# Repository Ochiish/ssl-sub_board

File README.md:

# SubBoard for SSL

## Overview

This is a sub-board installed in the SSL robot.
The boost circuit, neopixel, phototransistor, etc. are controlled by stm32, and CAN communication is performed with the main board.

## Requirement

- KiCad 7.0.5

## Usage

Good luck...

## Features

This is a sub-board installed in an SSL robot. The board is equipped with various components such as a boost circuit, NeoPixels, phototransistors, etc., all controlled by an STM32 microcontroller. 

- This microcontroller offers advanced programming and processing capabilities, efficiently managing the robot's diverse functions.

- The boost circuit optimizes power supply, ensuring each component on the board operates at the correct voltage. It elevates the low voltage from the battery, distributing power as needed.

- NeoPixels are individually controllable LEDs used for visual feedback and status indication on the robot. These LEDs can be customized in color and brightness through programming, intuitively conveying the robot's status to the operator.

- Phototransistors detect light intensity and convert this information into digital signals. This is a crucial sensor for environmental awareness and obstacle detection in the robot.

- Furthermore, this robot is equipped with a thermistor for measuring the temperature of the solenoid coil. The thermistor plays a vital role in monitoring the heat generated by the solenoid, preventing overheating and enhancing the robot's safety and equipment lifespan.

- Additionally, the sub-board incorporates protective circuits around the power supply, safeguarding it against overvoltage and short circuits. 

- These circuits are essential for maintaining power stability while minimizing electrical risks.

- The sub-board communicates with the main board using the CAN communication protocol. CAN communication is known for its high reliability and error detection capabilities, ensuring secure data exchange between different parts of the robot. This allows for smooth overall operation and the ability to perform more complex tasks.

In this way, the sub-board supports crucial functions of the SSL robot, drawing out the robot's maximum performance through advanced technology and meticulous design.

## Reference

https://www.analog.com/media/jp/technical-documentation/data-sheets/j3751fc.pdf

## Author

[@Allsatako](http://twitter.com/Allsatako)

mail to: rionesslq@gmail.com

## Licence

There is no license as this is open source hardware.

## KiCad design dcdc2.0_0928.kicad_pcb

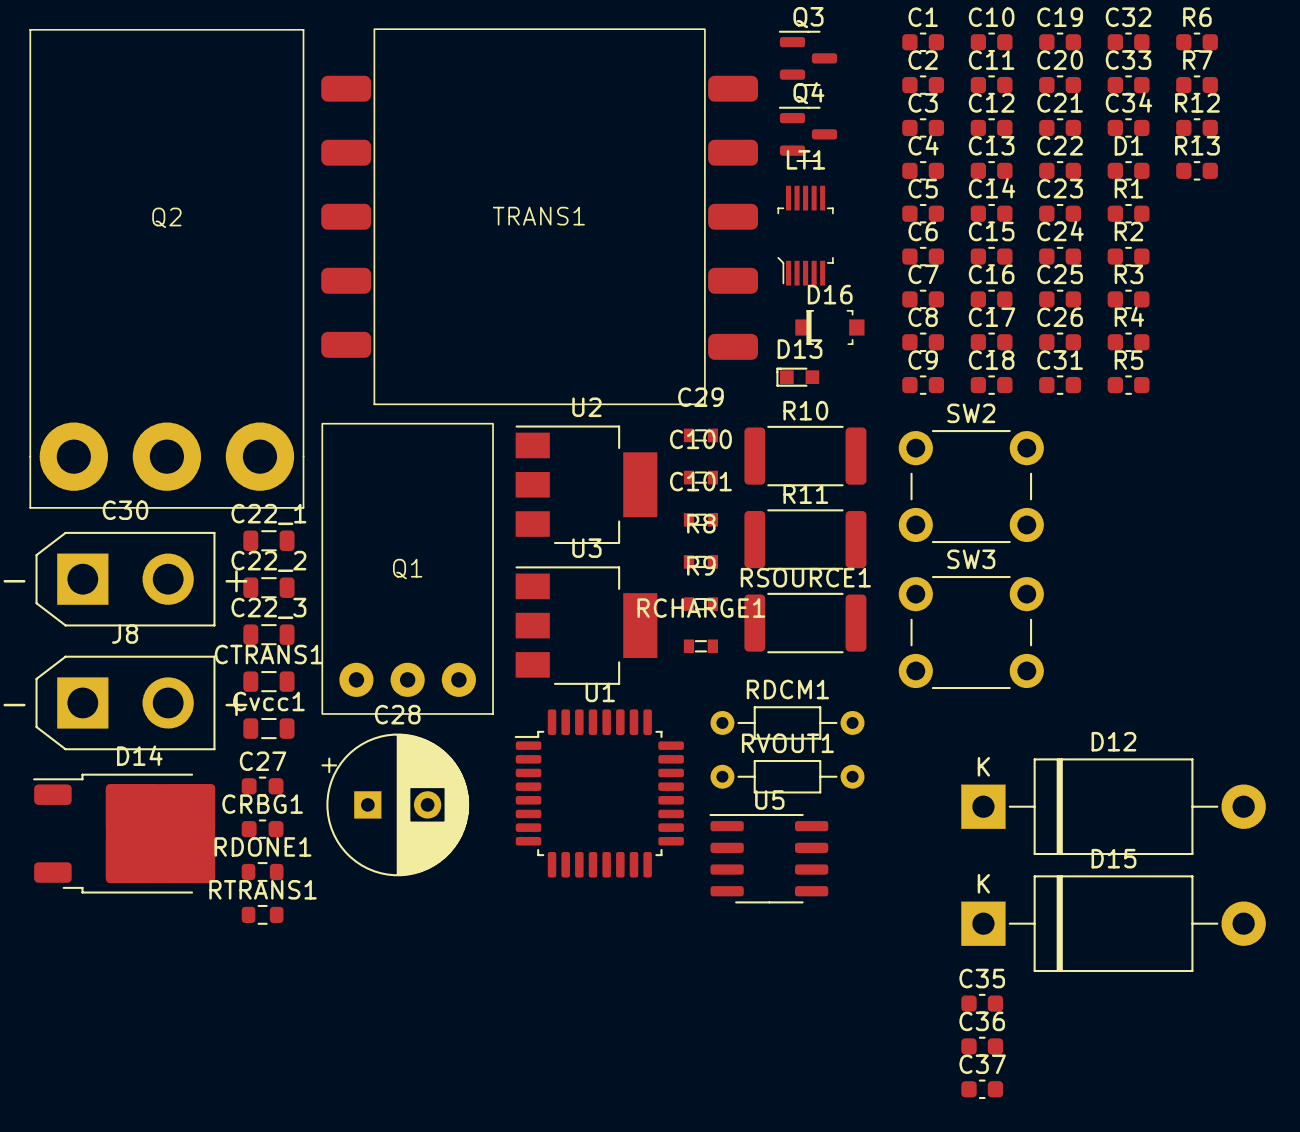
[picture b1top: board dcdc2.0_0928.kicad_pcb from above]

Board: 2 copper layers, 83 parts (0 on the bottom side), 33 nets, no tracks yet.

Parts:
C1, C2, C3, C4, C5, C6, C7, C11, C12, C13, C14, C15, C16, C17, C18, C19, C20, C21, C22, C23, C24, C25, C26, C32, C33, C34, C35, C36, C37: 0.1uF; C_0603_1608Metric
C8, C10: 4.3pF; C_0603_1608Metric
C9: 4.7uF; C_0603_1608Metric
C22_1, C22_2, C22_3: 22uF; L_0805_2012Metric
C27: 1000pf; L_0603_1608Metric
C28: 150uF 35v; CP_Radial_D8.0mm_P3.50mm
C29, C101: 0.1uF; 0603
C30: 2200uF; AMASS_XT30UPB-F_1x02_P5.0mm_Vertical
C31: 22uF; C_0603_1608Metric
C100: 10uF; 0603
CRBG1: 51pF; L_0603_1608Metric
CTRANS1: 10uF 50v; L_0805_2012Metric
Cvcc1: 10uF; L_0805_2012Metric
D1: LED; C_0603_1608Metric
D12, D15: 1.5KExxA; D_DO-201AE_P15.24mm_Horizontal
D13: LED; LED_0603
D14: 1N4007G; TO-252-2
D16: 1N47xxA; SOD-123
J8: Conn_01x02_Pin; AMASS_XT30UPB-F_1x02_P5.0mm_Vertical
LT1: MSOP-10_W3mm
Q1: tk20a60u
Q2: IRFP150NPbF
Q3, Q4: MMBT3906; SOT-23
R1, R2, R3, R6, R7: 10k; C_0603_1608Metric
R4: 470; C_0603_1608Metric
R5: 20k; C_0603_1608Metric
R8: 100Ω; 0603
R9: 1kΩ; 0603
R10, R11: 120Ω; R_2512_6332Metric
R12, R13: 5k; C_0603_1608Metric
RCHARGE1: 1kΩ; 0603
RDCM1: 42kΩ; R_Axial_DIN0204_L3.6mm_D1.6mm_P7.62mm_Horizontal
RDONE1: 100kΩ; R_0603_1608Metric
RSOURCE1: 0.01Ω; R_2512_6332Metric
RTRANS1: 0Ω; R_0603_1608Metric
RVOUT1: 30kΩ; R_Axial_DIN0204_L3.6mm_D1.6mm_P7.62mm_Horizontal
SW2, SW3: SW_MEC_5E; SW_PUSH_6mm
TRANS1: 32052
U1: STM32F303K8Tx; LQFP-32_7x7mm_P0.8mm
U2: V7805-1000; SOT-223-3_TabPin2
U3: AMS1117-5.0; SOT-223-3_TabPin2
U5: MCP2551-I-SN; SOIC-8_3.9x4.9mm_P1.27mm

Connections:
14v: C22_1.2, C22_2.2, C22_3.2, C28.2, Cvcc1.1, RTRANS1.1, TRANS1.4 (4IN), TRANS1.5 (5IN)
+3V3: C1.2, C3.2, C9.2, U1.1 (VDD), U1.5 (VDDA)
+5V: C4.1, C5.1, C6.1, C7.1, C11.1, C12.1, C13.1, C14.1, C15.1, C16.1, C17.1, C18.1, C19.1, C20.1, C21.1, C22.1, C23.1, C24.1, C25.1, C26.1, C100.2, C101.2, D15.1 (A1), R4.2, R12.1, R13.1, RDONE1.1, U5.3 (VDD)
/drain: RDCM1.2, RVOUT1.2, TRANS1.6 (6IN), TRANS1.7 (7IN)
/drain1: D16.2 (A), J8.2, Q2.3 (D)
/gate1: Q2.2 (G), R8.2, R9.2
/source: Q1.3 (S), RSOURCE1.2
/source1: Q2.1 (S), R9.1
CANH: R10.2, R11.1, U5.7 (CANH)
CANL: R10.1, R11.2, U5.6 (CANL)
CANRX: U1.21 (PA11), U5.4 (RXD)
CANTX: U1.22 (PA12), U5.1 (TXD)
CHARGE: C27.1, RCHARGE1.2
DIN: R3.1, U1.27 (PB4)
ENCODER_A: R12.2, U1.19 (PA9)
ENCODER_B: R13.2, U1.20 (PA10)
GND: C1.1, C2.1, C3.1, C4.2, C5.2, C6.2, C7.2, C8.2, C9.1, C10.2, C11.2, C12.2, C13.2, C14.2, C15.2, C16.2, C17.2, C18.2, C19.2, C20.2, C21.2, C22.2, C22_1.1, C22_2.1, C22_3.1, C23.2, C24.2, C25.2, C26.2, C27.2, C28.1, C32.2, C33.2, C34.2, C35.1, C36.2, C37.2, C100.1, C101.1, CRBG1.2, CTRANS1.1, Cvcc1.2, D1.1 (K), D13.1 (K), R2.1, R5.1, R6.2, R7.2, RSOURCE1.1, SW2.1, SW2.2, SW3.1, SW3.2, U1.16 (VSS), U1.32 (VSS), U3.1 (GND), U5.2 (VSS), U5.8 (Rs)
GND2: C29.1, C29.2, C30.1, C30.2, D14.1 (K), D16.1 (K), J8.1, TRANS1.10 (10OUT)
unnamed: C2.2, U1.17 (VDD)
unnamed: D1.2 (A), R1.2
unnamed: C34.1, C36.1, D12.2 (A2), U3.2 (VO)
unnamed: D13.2 (A), RCHARGE1.1
unnamed: D14.2 (A), TRANS1.1 (1OUT)
unnamed: C31.1, C32.1, C37.1, D15.2 (A2), U2.2 (VO), U3.3 (VI)
unnamed: Q4.2 (E), R7.1
unnamed: CTRANS1.2, RTRANS1.2
unnamed: Q3.1 (B), Q3.3 (C), Q4.1 (B), R6.1
unnamed: R2.2, U1.31 (BOOT0)
unnamed: R1.1, U1.30 (PB7)
unnamed: C31.2, U2.1 (GND)
unnamed: C35.2, U2.3 (VI)
SYS-SWDIO: U1.23 (PA13), U1.26 (PB3)
TR_SIG: R5.2, U1.6 (PA0)

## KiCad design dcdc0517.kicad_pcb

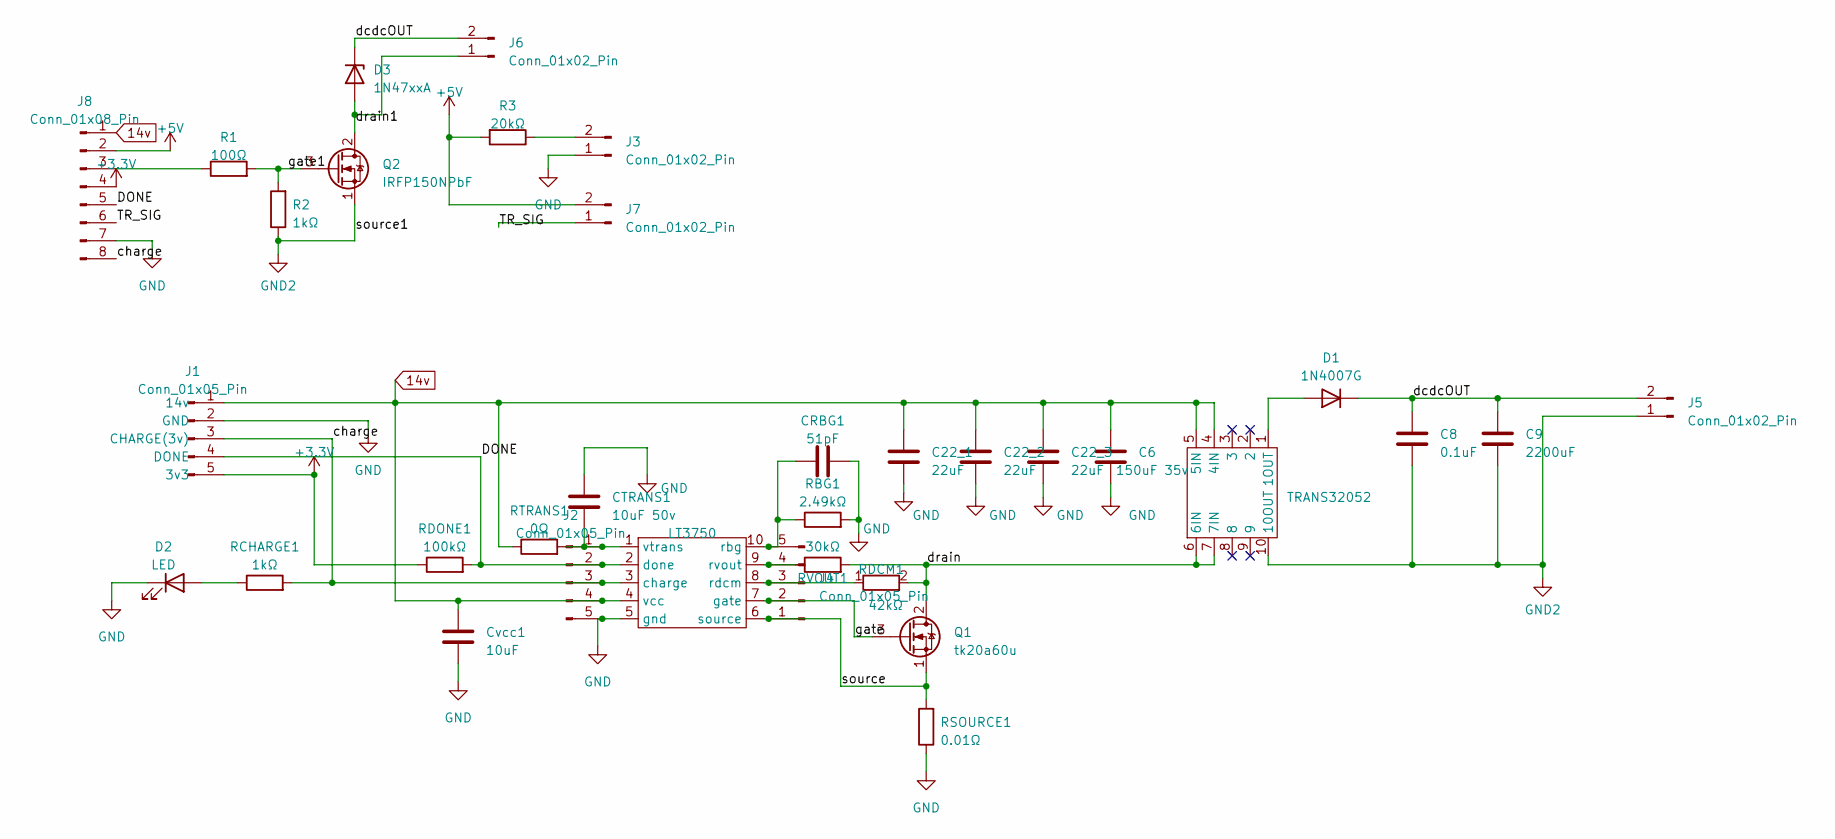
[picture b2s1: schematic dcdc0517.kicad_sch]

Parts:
C6: 150uF 35v; CP_Radial_D8.0mm_P3.50mm
C8: 0.1uF; PinHeader_1x02_P2.54mm_Vertical
C9: 2200uF; AMASS_XT30UPB-F_1x02_P5.0mm_Vertical
C22_1, C22_2, C22_3: 22uF; L_0805_2012Metric
CRBG1: 51pF; L_0603_1608Metric
CTRANS1: 10uF 50v; L_0805_2012Metric
Cvcc1: 10uF; L_0805_2012Metric
D1: 1N4007G; D_DO-35_SOD27_P7.62mm_Horizontal
D2: LED; LED_D3.0mm_FlatTop
D3: 1N47xxA; D_DO-41_SOD81_P10.16mm_Horizontal
J1, J2, J4: Conn_01x05_Pin; PinHeader_1x05_P2.54mm_Vertical
J3, J7: Conn_01x02_Pin; PinHeader_1x02_P2.54mm_Vertical
J5, J6: Conn_01x02_Pin; AMASS_XT30UPB-F_1x02_P5.0mm_Vertical
J8: Conn_01x08_Pin; JST_XH_B8B-XH-AM_1x08_P2.50mm_Vertical
LT3750: MSOP-10_W3mm
Q1: tk20a60u; PinHeader_1x3_P2.54_Drill1.1mm
Q2: IRFP150NPbF; TERM_BLOCK_1x3_P5.08MM
R1: 100Ω; R_0603_1608Metric
R2: 1kΩ; R_0603_1608Metric
R3: 20kΩ; R_0201_0603Metric
RBG1: 2.49kΩ; R_Axial_DIN0204_L3.6mm_D1.6mm_P7.62mm_Horizontal
RCHARGE1: 1kΩ; 0603
RDCM1: 42kΩ; R_Axial_DIN0204_L3.6mm_D1.6mm_P7.62mm_Horizontal
RDONE1: 100kΩ; R_0201_0603Metric
RSOURCE1: 0.01Ω; R_Shunt_Vishay_WSR2_WSR3
RTRANS1: 0Ω; R_Axial_DIN0204_L3.6mm_D1.6mm_P7.62mm_Horizontal
RVOUT1: 30kΩ; R_Axial_DIN0204_L3.6mm_D1.6mm_P7.62mm_Horizontal
TRANS32052: 32052

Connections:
14v: C6.1, C22_1.1, C22_2.1, C22_3.1, Cvcc1.1, J1.1 (14v), J2.4 (vcc), J8.1, LT3750.4 (vcc), RTRANS1.1, TRANS32052.4 (4IN), TRANS32052.5 (5IN)
+3.3V: J1.5 (3v3), J8.4, RDONE1.1
+5V: J7.2, J8.2, R3.2
/DONE: J1.4 (DONE), J2.2 (done), J8.5, LT3750.2 (done), RDONE1.2
/TR_SIG: J7.1, J8.6
/charge: J1.3 (CHARGE(3v)), J2.3 (charge), J8.8, LT3750.3 (charge), RCHARGE1.2
/dcdcOUT: C8.2, C9.2, D1.1 (K), D3.1 (K), J5.2, J6.2
/drain: Q1.2 (D), RDCM1.2, RVOUT1.2, TRANS32052.6 (6IN), TRANS32052.7 (7IN)
/drain1: D3.2 (A), J6.1, Q2.2 (D)
/gate: J4.2 (gate), LT3750.7 (gate), Q1.3 (G)
/gate1: Q2.3 (G), R1.2, R2.2
/source: J4.1 (source), LT3750.6 (source), Q1.1 (S), RSOURCE1.2
GND: C6.2, C22_1.2, C22_2.2, C22_3.2, CRBG1.2, CTRANS1.1, Cvcc1.2, D2.1 (K), J1.2 (GND), J2.5 (gnd), J3.1, J8.7, LT3750.5 (gnd), RBG1.2, RSOURCE1.1
GND2: C8.1, C9.1, J5.1, Q2.1 (S), R2.1, TRANS32052.10 (10OUT)
unnamed: D1.2 (A), TRANS32052.1 (1OUT)
unnamed: D2.2 (A), RCHARGE1.1
unnamed: CTRANS1.2, J2.1 (vtrans), LT3750.1 (vtrans), RTRANS1.2
unnamed: J3.2, R3.1
unnamed: CRBG1.1, J4.5 (rbg), LT3750.10 (rbg), RBG1.1
unnamed: J4.3 (rdcm), LT3750.8 (rdcm), RDCM1.1
unnamed: J4.4 (rvout), LT3750.9 (rvout), RVOUT1.1
unnamed: J8.3, R1.1

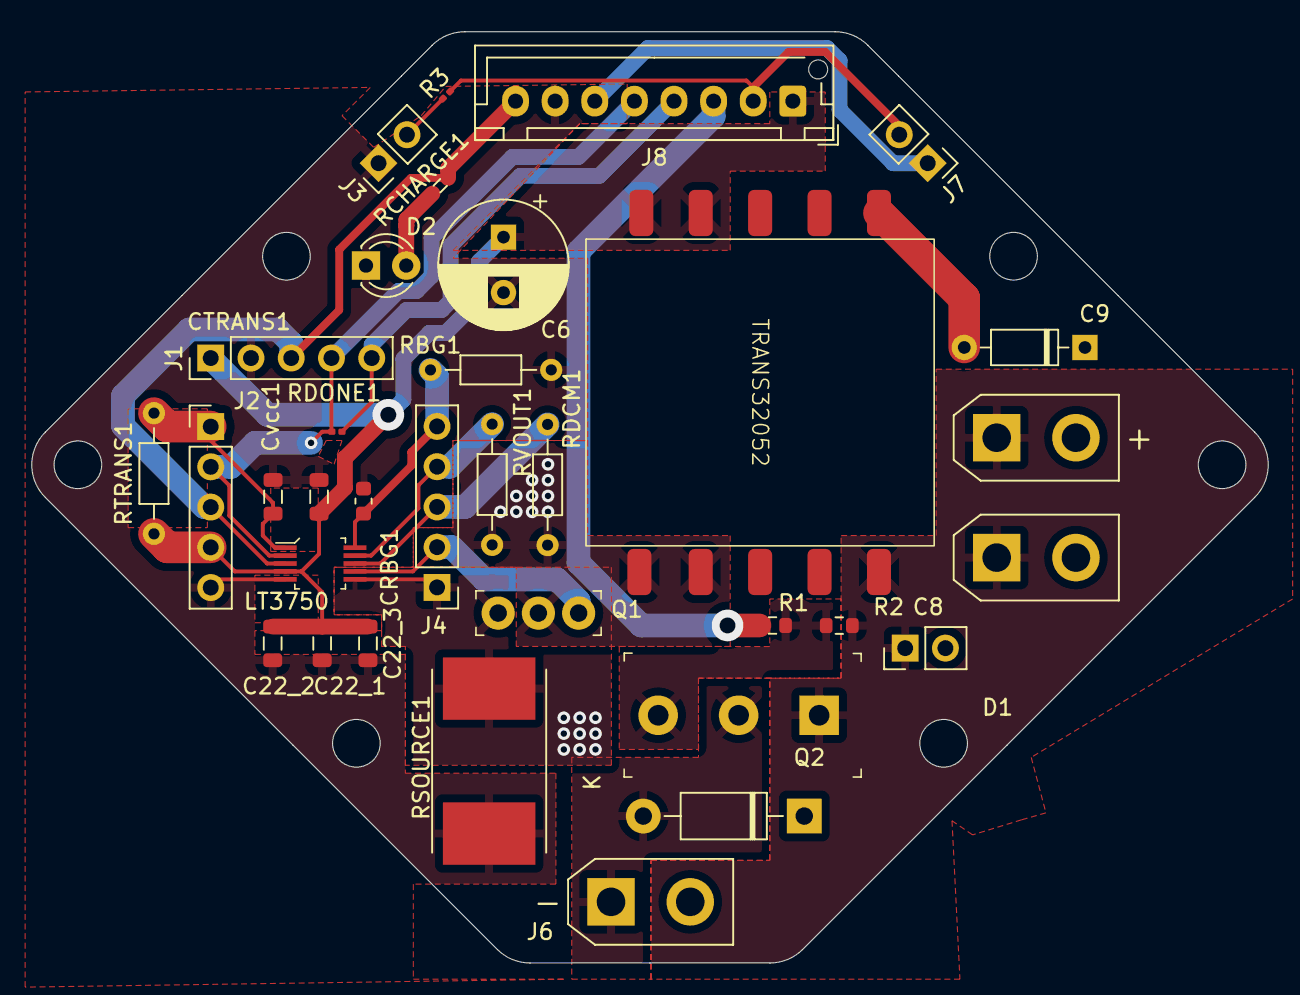
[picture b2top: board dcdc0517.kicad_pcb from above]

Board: 2 copper layers, 78.0 x 58.8 mm, 34 parts (0 on the bottom side), 22 nets.

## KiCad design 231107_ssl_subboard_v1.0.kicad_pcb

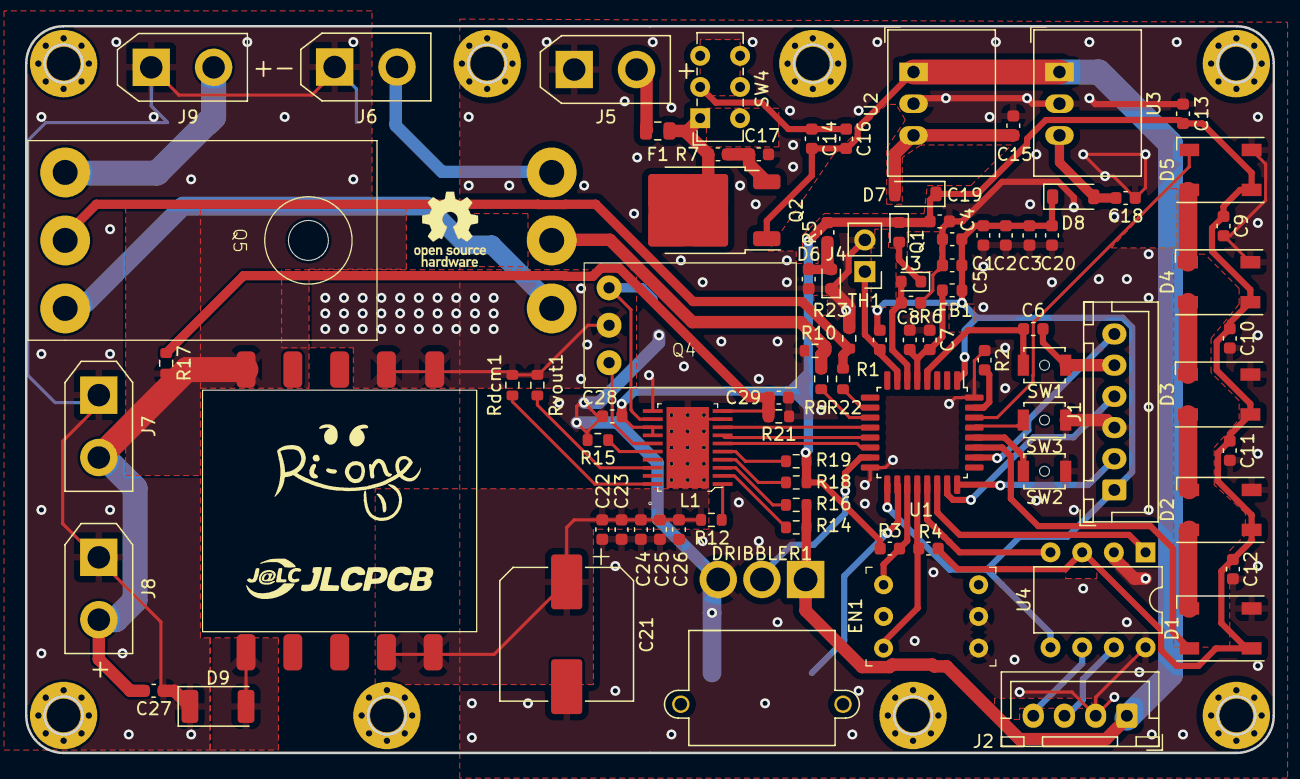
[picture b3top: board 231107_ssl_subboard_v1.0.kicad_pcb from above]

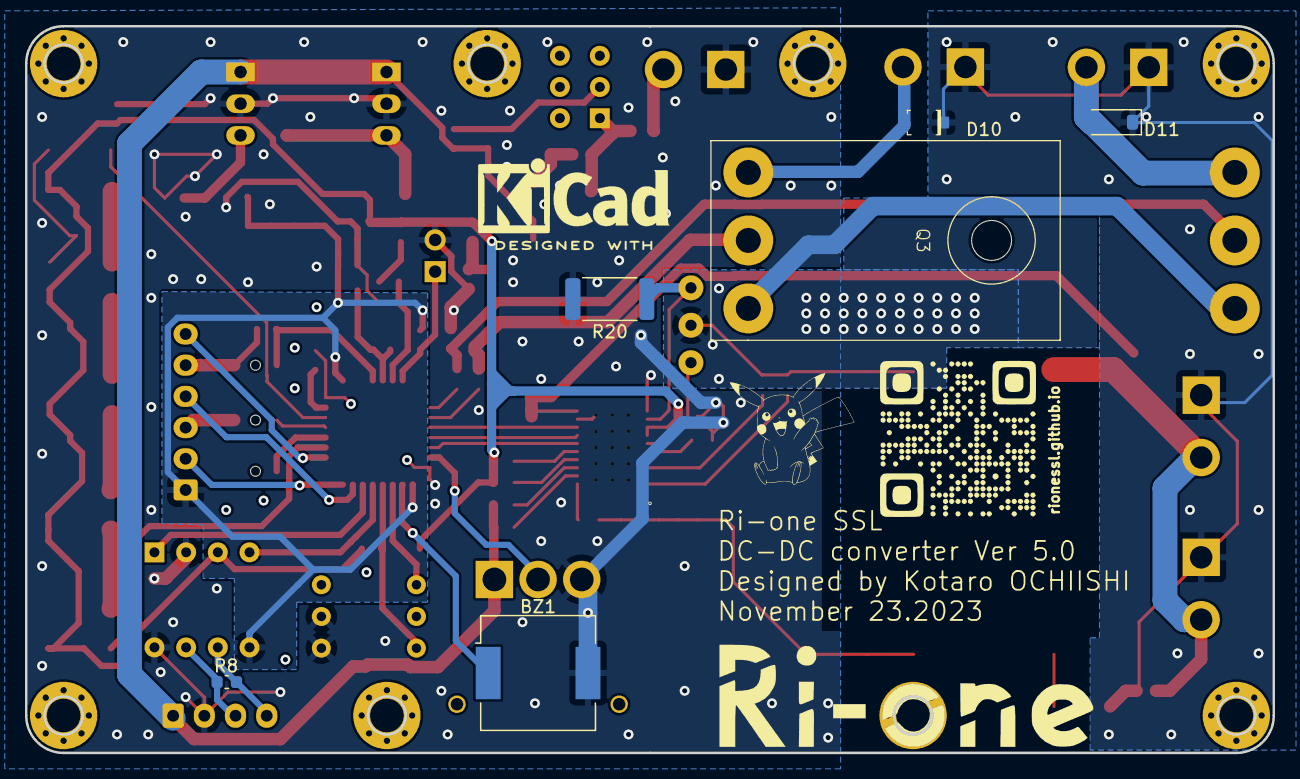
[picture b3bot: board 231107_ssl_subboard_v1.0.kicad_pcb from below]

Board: 2 copper layers, 100.0 x 58.2 mm, 93 parts (6 on the bottom side), 62 nets.

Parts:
BZ1: Buzzer; Buzzer_CUI_CPT-9019S-SMT
C1, C2, C3, C4, C5, C6, C7, C8, C9, C10, C11, C12, C13, C14, C16, C17, C19, C20: 0.1uF; C_0603_1608Metric
C15, C18, C22, C23, C24, C25, C26: 2.2u; C_0603_1608Metric
C21: 680u; CP_Elec_10x10.5
C27: 0.47u; C_0603_1608Metric
C28, C29: 10n; C_0603_1608Metric
D1, D2, D3, D4, D5: ws2812b; LED_Cree-PLCC4_5x5mm_CW
D6: LED; C_0603_1608Metric
D7, D8: SS2040FL; D_SOD-123
D9: 1.5KExxA; D_2010_5025Metric
D10: 1.5KExxA; SOD-123
D11: 1.5KExxA; D_SOD-123
DRIBBLER1: MR30PW-M; AMASS_MR30PW-M_1x03_P3.50mm_Horizontal
EN1: RotaryEncoder_Switch; SOCKET_DIP-6_7.62mm_Conn
F1: Fuse; Fuse_0805_2012Metric
FB1: FerriteBead_Small; L_0603_1608Metric
J1: pc to stm32; JST_XH_B6B-XH-A_1x06_P2.50mm_Vertical
J2: main to sub; JST_XH_B4B-XH-A_1x04_P2.50mm_Vertical
J3: PHOTOCOUPLER; LED_0603_1608Metric
J4: LED; LED_0603_1608Metric
J5: lipo_3cell; AMASS_XT30UPB-M_1x02_P5.0mm_Vertical
J6: s1; AMASS_XT30UPB-F_1x02_P5.0mm_Vertical
J7: c1; AMASS_XT30UPB-F_1x02_P5.0mm_Vertical
J8: c2; AMASS_XT30UPB-F_1x02_P5.0mm_Vertical
J9: s2; AMASS_XT30UPB-F_1x02_P5.0mm_Vertical
L1: TSSOP-20-1EP_W4.4mm
Q1: Q_Photo_NPN; LED_0603_1608Metric
Q2: PMOS; TO-252-2
Q3, Q5: NMOS; IRFP150NPbF
Q4: Q_NMOS_DGS; tk20a60u
R1, R3, R4: 5k; C_0603_1608Metric
R2, R7: 10k; C_0603_1608Metric
R5: 470; C_0603_1608Metric
R6: 20k; C_0603_1608Metric
R8: 120; C_0603_1608Metric
R9, R22: 100; R_0603_1608Metric
R10, R23: 1k; R_0603_1608Metric
R12: 40.2k; R_0603_1608Metric
R14, R18: 69.8k; R_0603_1608Metric
R15: 1.65; R_0603_1608Metric
R16, R19: 475k; R_0603_1608Metric
R17: 124; R_0603_1608Metric
R20: 6m; R_2512_6332Metric
R21: 0.768k; R_0603_1608Metric
Rdcm1: 18.2k; R_0603_1608Metric
Rvout1: 40.2k; R_0603_1608Metric
SW1, SW2, SW3: SW_Push; SW_SPST_B3U-1000P-B
SW4: SW_SPST; SW_E-Switch_EG1271_SPDT
TH1: Thermistor; PinHeader_1x02_P2.54mm_Vertical
U1: STM32F303K8Tx; LQFP-32_7x7mm_P0.8mm
U2: M78AR05-1; Converter_DCDC_RECOM_R-78E-0.5_THT
U3: M78AR033-1; Converter_DCDC_RECOM_R-78E-0.5_THT
U4: MCP2562-E-P; DIP-8_W7.62mm
U5: 32052

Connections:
+3V3: C1.2, C2.2, C3.2, C4.2, C5.2, C20.2, D8.1 (K), FB1.1, J1.1, R1.2, U1.1 (VDD), U1.17 (VDD), U4.5 (Vio)
+5V: C9.1, C10.1, C11.1, C12.1, C13.1, C19.2, C28.1, D1.3 (VDD), D2.3 (VDD), D3.3 (VDD), D4.3 (VDD), D5.3 (VDD), D7.1 (K), L1.13 (VCC), L1.14 (LVGATE), Q1.1 (C), R3.1, R4.1, R5.2, R18.1, R19.1, U4.3 (VDD)
+15V: C14.2, C16.2, DRIBBLER1.1, J2.1, Q2.1 (D), R14.1, R16.1, U2.1 (IN), U3.1 (IN)
+BATT: F1.1, J5.2
CANH: J2.3, R8.2, U4.7 (CANH)
CANL: J2.4, R8.1, U4.6 (CANL)
CANRX: U1.21 (PA11), U4.4 (RXD)
CANTX: U1.22 (PA12), U4.1 (TXD)
CHARGE: L1.8 (CHARGE), U1.12 (PA6)
Cvtrans: C21.1, C22.1, C23.1, C24.1, C25.1, C26.1, R12.1, U5.4 (4IN), U5.5 (5IN)
DCDC_OUT: C27.1, D9.1 (A1), D10.1 (A1), D11.1 (A1), J6.1, J7.1, J8.1, J9.1
DIN: D1.4 (DIN), U1.27 (PB4)
DONE: L1.7 (DONE), U1.13 (PA7)
DOUT: D5.1 (DOUT), U1.30 (PB7)
DR_PWM: DRIBBLER1.2, U1.15 (PB1)
DR_SW: SW3.2, U1.29 (PB6)
Drain: Q4.1 (D), Rdcm1.2, Rvout1.2, U5.6 (6IN), U5.7 (7IN)
ENCODER_A: EN1.1 (A), R3.2, U1.19 (PA9)
ENCODER_B: EN1.3 (B), R4.2, U1.20 (PA10)
FAULT: L1.6 (FAULT), U1.14 (PB0)
GND: BZ1.2 (+), C1.1, C2.1, C3.1, C4.1, C5.1, C7.1, C8.1, C9.2, C10.2, C11.2, C12.2, C13.2, C15.1, C17.1, C18.1, C19.1, C20.1, C21.2, C22.2, C23.2, C24.2, C25.2, C26.2, C28.2, C29.2, D1.2 (GND), D2.2 (GND), D3.2 (GND), D4.2 (GND), D5.2 (GND), D6.1 (K), DRIBBLER1.3, EN1.4 (S1), EN1.5 (S2), J1.3, J2.2, J4.1, J5.1, L1.9 (CLAMP), L1.11 (CSN), L1.21 (GND), Q3.3 (S), Q5.3 (S), R2.1, R6.2, R10.1, R15.2, R20.2, R21.1, R23.1, SW2.1, SW3.1, TH1.2, U1.16 (VSS), U1.32 (VSS), U2.2 (GND), U3.2 (GND), U4.2 (VSS), U4.8 (STBY)
KICK_SW: SW2.2, U1.28 (PB5)
NRST: C6.1, J1.5, SW1.1
unnamed: BZ1.1 (-), U1.18 (PA8)
unnamed: D1.1 (DOUT), D2.4 (DIN)
unnamed: D2.1 (DOUT), D3.4 (DIN)
unnamed: D3.1 (DOUT), D4.4 (DIN)
unnamed: D4.1 (DOUT), D5.4 (DIN)
unnamed: D6.2 (A), J4.2, R5.1
unnamed: C15.2, D7.2 (A), U2.3 (OUT)
unnamed: C18.2, D8.2 (A), U3.3 (OUT)
unnamed: D10.2 (A2), J6.2, Q3.1 (D)
unnamed: D11.2 (A2), J9.2, Q5.1 (D)
unnamed: J3.1, Q1.2 (E)
unnamed: L1.12 (CSP), Q4.3 (S), R20.1
unnamed: C29.1, L1.10 (FB), R17.1, R21.2
unnamed: L1.15 (HVGATE), Q4.2 (G)
unnamed: L1.3 (OVLO1), R16.2
unnamed: L1.5 (OVLO2), R19.2
unnamed: L1.16 (RBG), R15.1
unnamed: L1.20 (RDCM), Rdcm1.1
unnamed: L1.18 (RVOUT), Rvout1.1
unnamed: L1.1 (RVTRANS), R12.2
unnamed: L1.2 (UVLO1), R14.2
unnamed: L1.4 (UVLO2), R18.2
unnamed: F1.2, Q2.2 (G), R7.2, SW4.1 (A)
unnamed: C17.2, Q2.3 (S), R7.1
unnamed: Q3.2 (G), R9.2, R10.2
unnamed: Q5.2 (G), R22.2, R23.2
unnamed: C14.1, C16.1, SW4.2 (B)
unnamed: R2.2, U1.31 (BOOT0)
unnamed: C6.2, SW1.2, U1.4 (NRST)
unnamed: R1.1, TH1.1, U1.7 (PA1)
unnamed: C7.2, C8.2, FB1.2, U1.5 (VDDA)
STRAIGHT: R9.1, U1.11 (PA5)
SYS-SWCLK: J1.2, U1.24 (PA14)
SYS-SWDIO: J1.4, U1.23 (PA13)
SYS-SWO: J1.6, U1.26 (PB3)
TR_SIG: J3.2, R6.1, U1.6 (PA0)
Vout: D9.2 (A2), U5.1 (1OUT)
tip: R22.1, U1.10 (PA4)
trans2: C27.2, J7.2, J8.2, R17.2, U5.10 (10OUT)

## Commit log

2023-02-23 second commit
2023-02-24 third commit
2023-03-04 commit4
2023-03-04 commit6
2023-04-21 test0422
2023-05-24 Add files via upload
    designed with kicad
2023-06-27 last circuit
2023-11-29 add .gitignore
2023-11-29 add imagefile
2023-11-29 add newimage
